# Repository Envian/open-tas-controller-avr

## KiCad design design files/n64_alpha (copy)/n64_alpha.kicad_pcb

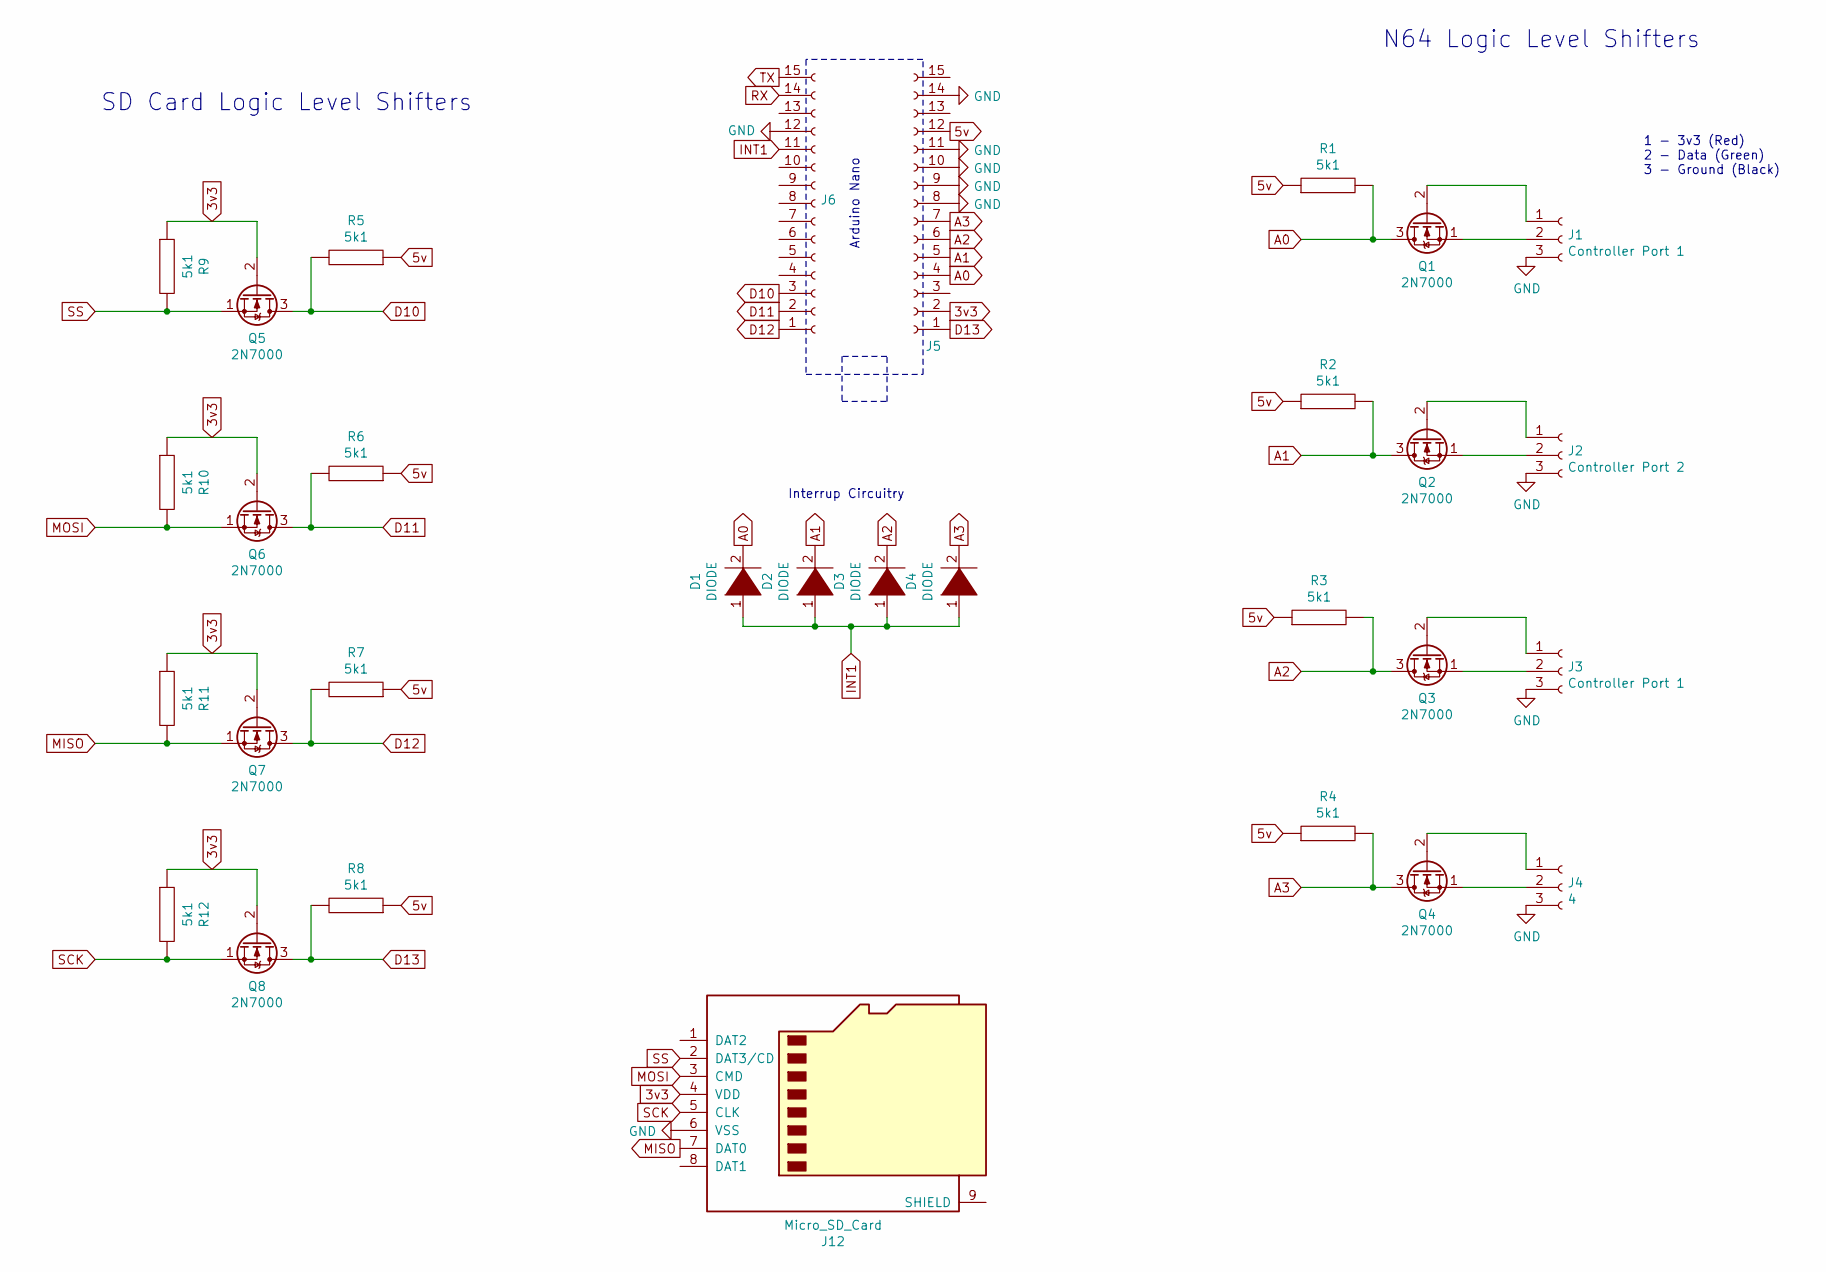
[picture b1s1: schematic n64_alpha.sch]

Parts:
D1, D2, D3, D4: DIODE; R_Axial_DIN0207_L6.3mm_D2.5mm_P10.16mm_Horizontal
J1, J3: Controller Port 1; JST_XH_S3B-XH-A_1x03_P2.50mm_Horizontal
J2: Controller Port 2; JST_XH_S3B-XH-A_1x03_P2.50mm_Horizontal
J4: 4; JST_XH_S3B-XH-A_1x03_P2.50mm_Horizontal
J5, J6: Conn_01x15_Female; PinHeader_1x15_P1.00mm_Vertical
J12: Micro_SD_Card; microSD_HC_Hirose_DM3D-SF
Q1, Q2, Q3, Q4, Q5, Q6, Q7, Q8: 2N7000; TO-92_Inline
R1, R2, R3, R4, R5, R6, R7, R8, R9, R10, R11, R12: 5k1; R_Axial_DIN0207_L6.3mm_D2.5mm_P10.16mm_Horizontal

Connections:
3v3: J5.2, J12.4 (VDD), Q5.2 (G), Q6.2 (G), Q7.2 (G), Q8.2 (G), R9.1, R10.1, R11.1, R12.1
5v: J5.12, R1.1, R2.1, R3.1, R4.1, R5.1, R6.1, R7.1, R8.1
A0: D1.2 (A), J5.4, Q1.3 (D), R1.2
A1: D2.2 (A), J5.5, Q2.3 (D), R2.2
A2: D3.2 (A), J5.6, Q3.3 (D), R3.2
A3: D4.2 (A), J5.7, Q4.3 (D), R4.2
D10: J6.3, Q5.3 (D), R5.2
D11: J6.2, Q6.3 (D), R6.2
D12: J6.1, Q7.3 (D), R7.2
D13: J5.1, Q8.3 (D), R8.2
GND: J1.3, J2.3, J3.3, J4.3, J5.8, J5.9, J5.10, J5.11, J5.14, J6.12, J12.6 (VSS)
INT1: D1.1 (K), D2.1 (K), D3.1 (K), D4.1 (K), J6.11
MISO: J12.7 (DAT0), Q7.1 (S), R11.2
MOSI: J12.3 (CMD), Q6.1 (S), R10.2
unnamed: J1.1, Q1.2 (G)
unnamed: J1.2, Q1.1 (S)
unnamed: J2.1, Q2.2 (G)
unnamed: J2.2, Q2.1 (S)
unnamed: J3.1, Q3.2 (G)
unnamed: J3.2, Q3.1 (S)
unnamed: J4.1, Q4.2 (G)
unnamed: J4.2, Q4.1 (S)
RX: J6.14
SCK: J12.5 (CLK), Q8.1 (S), R12.2
SS: J12.2 (DAT3/CD), Q5.1 (S), R9.2
TX: J6.15

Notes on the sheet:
1 - 3v3 (Red) 2 - Data (Green) 3 - Ground (Black)
Arduino Nano
N64 Logic Level Shifters
SD Card Logic Level Shifters
Interrup Circuitry

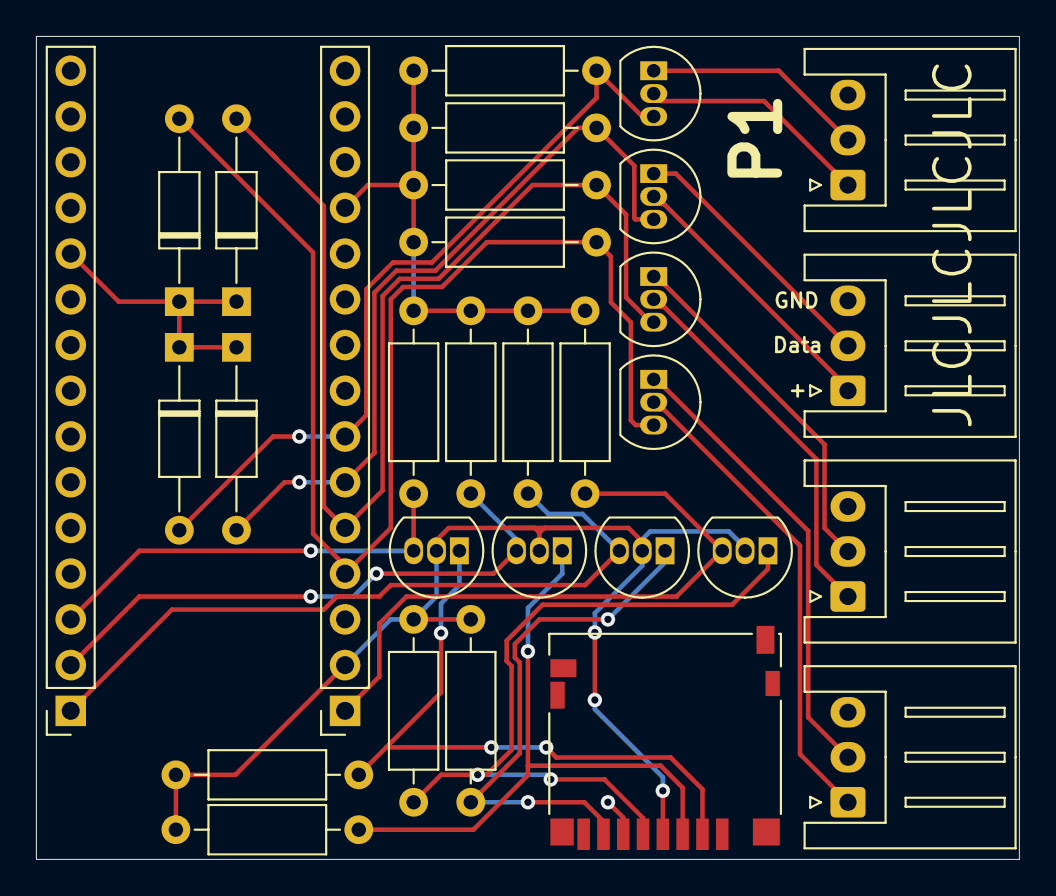
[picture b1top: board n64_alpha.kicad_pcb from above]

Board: 2 copper layers, 54.6 x 45.7 mm, 31 parts (0 on the bottom side), 24 nets.

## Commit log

2019-06-19 Changing file format
2019-06-19 Fixing issues with rumble enabled games
2019-06-21 Updates to convert script, added a flash cart injector
2019-06-26 Beginning refactor for Arduino Nano
2019-06-26 Adding framework for console playback
2019-06-26 Moving common settings to lib
2019-06-30 Adding port determination and initial console work
2019-07-30 Rewrite of core controller to AVR (Arduino Nano)
2019-07-30 Fixing issues and adding a core loop
2019-07-30 Removed blocking error handler. Fixed headers, warnings
2019-08-01 Now working
2019-08-10 Began implementing the full console playback
2019-08-14 Adding sanity check before movie playback
2019-08-14 Beginning work on module-based file format parsers
2019-08-14 Added a bit more flexibility in how formats are detected
2019-08-15 Adding format auto detect
2019-08-15 Fixing loading issues
2019-08-15 Added parsing metadata out of mupen files
2019-08-15 Implemented basic metadata display
2019-08-15 Added progress bar
2019-08-16 Corrected frame counter
2019-08-16 Cleaning up main class and separating formats from file loading
2019-08-16 Reworking arguments
2019-08-16 Adding support for reading from linux pipe
2019-08-24 Splitting record and playback logic
2019-08-27 MVP for movie recording
2019-08-27 Adding support for lesser used controller commands
2019-08-30 refactoring PC Front end, temporarily broke recording
2019-08-30 Adding auto-extract functionality
2020-02-02 Adding support for parsing bizhawk replays - Not working yet?
2020-10-06 First pass on recording movies
2020-10-17 Did some work after coming back
2020-10-18 Adding ignore for warning
2020-10-26 Update to use more well structured command based API
2020-10-30 Improving error handling, messages, and some code tweaks
2020-10-30 Adding prototype board
2020-10-30 Updating some commands for easier terminal use
2020-11-02 Updated a few commands to better support movie recording in the short term future
2020-11-02 Making strings newline-terminated, plus updating how data strings are handled
2020-11-02 Adding initial recording code
2020-11-02 Recording Works! For some games
